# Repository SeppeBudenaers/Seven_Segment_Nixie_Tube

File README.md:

# Seven Segment Nixie Tube
 This repository contains the code and design files for a LED filament seven segment display, designed to resemble a nixie tube. The display can be configured in either common anode or WS2811 mode, providing a modern twist on the classic nixie tube aesthetic. It provides a warm glow to resemble a nixie tube while taking advantage of LED technology. Explore the provided files to build your own LED filament seven segment display and infuse your projects with a touch of vintage charm.
## How to use it 
To configure the LED filament seven segment display to common anode mode, solder the first and second pads of every solder bridge together.

To configure the LED filament seven segment display to WS2811 mode, solder the second and third pads of every solder bridge together.
## Bill of Material
### common anode mode

| Item                                   | Quantity | Link                                                                                                                                                       |
|----------------------------------------|----------|------------------------------------------------------------------------------------------------------------------------------------------------------------|
| Glas tube 30x60mm                      | x1       | [AliExpress Link](https://nl.aliexpress.com/item/32813289039.html?spm=a2g0o.order_list.order_list_main.5.21ef79d2e9LWZz&gatewayAdapt=glo2nld)                    |
| Red LED filament                       | x7       | [AliExpress Link](https://nl.aliexpress.com/item/1005003834518235.html?spm=a2g0o.order_list.order_list_main.10.21ef79d2e9LWZz&gatewayAdapt=glo2nld-)              |
| 47 ohm resistors                       | x7       | [LCSC Link](https://www.lcsc.com/product-detail/_UNI-ROYAL-Uniroyal-Elec-_C25315.html)                                                                    |
| 8 2,54mm pinheader reverse bending 90° | x1       | [AliExpress Link](https://nl.aliexpress.com/item/4000660389713.html?spm=a2g0o.productlist.main.5.6b8d804dlred9v&algo_pvid=283ea269-678a-498f-bd60-9fb64c34b0f6&algo_exp_id=283ea269-678a-498f-bd60-9fb64c34b0f6-2&pdp_npi=3%40dis%21EUR%210.67%210.62%21%21%21%21%21%402100b18f16839900715117374d078a%2110000005517155325%21sea%21BE%213754600235&curPageLogUid=IQMuIH5lTEpR) |

### WS2811 mode

| Item                                   | Quantity | Link                                                                                                                                                       |
|----------------------------------------|----------|------------------------------------------------------------------------------------------------------------------------------------------------------------|
| Glas tube 30x60mm                      | x1       | [AliExpress Link](https://nl.aliexpress.com/item/32813289039.html?spm=a2g0o.order_list.order_list_main.5.21ef79d2e9LWZz&gatewayAdapt=glo2nld)                    |
| Red LED filament                       | x7       | [AliExpress Link](https://nl.aliexpress.com/item/1005003834518235.html?spm=a2g0o.order_list.order_list_main.10.21ef79d2e9LWZz&gatewayAdapt=glo2nld)              |
| 47 ohm resistor                        | x7       | [LCSC Link](https://www.lcsc.com/product-detail/_UNI-ROYAL-Uniroyal-Elec-_C25315.html)                                                                    |
| 100 ohm resistor                       | x3       | [LCSC Link](https://www.lcsc.com/product-detail/_UNI-ROYAL-Uniroyal-Elec-_C17408.html)                                                                    |
| WS2811                                 | x3       | [LCSC Link](https://www.lcsc.com/product-detail/LED-Drivers_Worldsemi-WS2811_C114581.html)                                                                |
| 8 2,54mm pinheader reverse bending 90° | x1       | [AliExpress Link](https://nl.aliexpress.com/item/4000660389713.html?spm=a2g0o.productlist.main.5.6b8d804dlred9v&algo_pvid=283ea269-678a-498f-bd60-9fb64c34b0f6&algo_exp_id=283ea269-678a-498f-bd60-9fb64c34b0f6-2&pdp_npi=3%40dis%21EUR%210.67%210.62%21%21%21%21%21%402100b18f16839900715117374d078a%2110000005517155325%21sea%21BE%213754600235&curPageLogUid=IQMuIH5lTEpR) |

## todo
- [ ] Add media.
- [ ] Write a library for arduino to use my segments in WS2811 mode.

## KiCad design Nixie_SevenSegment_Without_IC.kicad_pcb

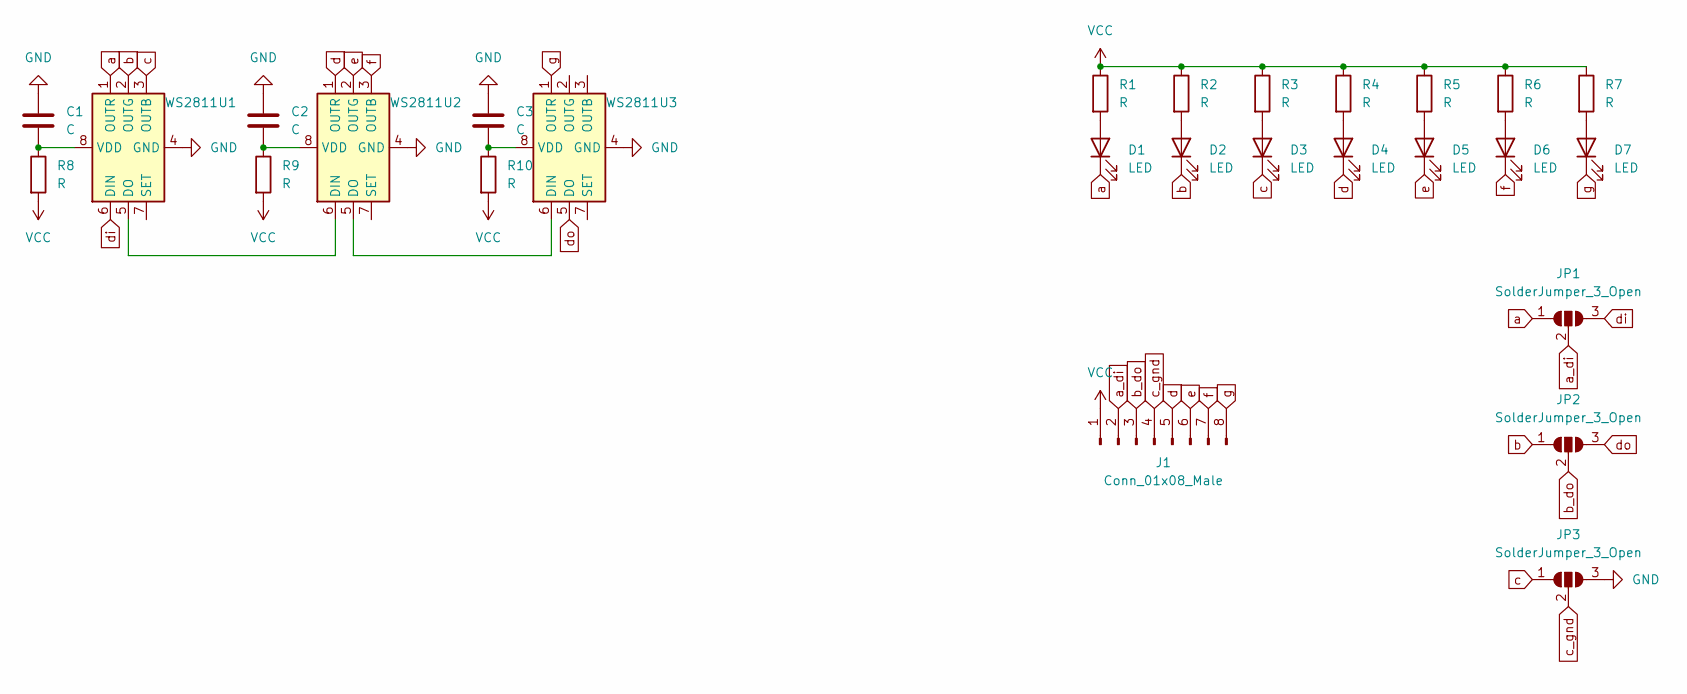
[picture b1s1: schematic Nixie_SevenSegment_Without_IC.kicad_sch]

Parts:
C1, C2, C3: C; C_0805_2012Metric_Pad1.18x1.45mm_HandSolder
D1, D2, D3, D4, D5, D6, D7: LED; LEDFilament_12mm
J1: Conn_01x08_Male; PinSocket_1x08_P2.54mm_Vertical
JP1, JP2, JP3: SolderJumper_3_Open; SolderJumper-3_P1.3mm_Open_Pad1.0x1.5mm
R1, R2, R3, R4, R5, R6, R7, R8, R9, R10: R; R_0805_2012Metric_Pad1.20x1.40mm_HandSolder
U1, U2, U3: WS2811; SOP-8_3.9x4.9mm_P1.27mm

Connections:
GND: C1.2, C2.2, C3.2, JP3.3 (B), U1.4 (GND), U2.4 (GND), U3.4 (GND)
unnamed: C1.1, R8.1, U1.8 (VDD)
unnamed: C2.1, R9.1, U2.8 (VDD)
unnamed: C3.1, R10.1, U3.8 (VDD)
unnamed: D1.2 (A), R1.2
unnamed: D2.2 (A), R2.2
unnamed: D3.2 (A), R3.2
unnamed: D4.2 (A), R4.2
unnamed: D5.2 (A), R5.2
unnamed: D6.2 (A), R6.2
unnamed: D7.2 (A), R7.2
unnamed: U1.5 (DO), U2.6 (DIN)
unnamed: U2.5 (DO), U3.6 (DIN)
VCC: J1.1, R1.1, R2.1, R3.1, R4.1, R5.1, R6.1, R7.1, R8.2, R9.2, R10.2
a: D1.1 (K), JP1.1 (A), U1.1 (OUTR)
a_di: J1.2, JP1.2 (C)
b: D2.1 (K), JP2.1 (A), U1.2 (OUTG)
b_do: J1.3, JP2.2 (C)
c: D3.1 (K), JP3.1 (A), U1.3 (OUTB)
c_gnd: J1.4, JP3.2 (C)
d: D4.1 (K), J1.5, U2.1 (OUTR)
di: JP1.3 (B), U1.6 (DIN)
do: JP2.3 (B), U3.5 (DO)
e: D5.1 (K), J1.6, U2.2 (OUTG)
f: D6.1 (K), J1.7, U2.3 (OUTB)
g: D7.1 (K), J1.8, U3.1 (OUTR)

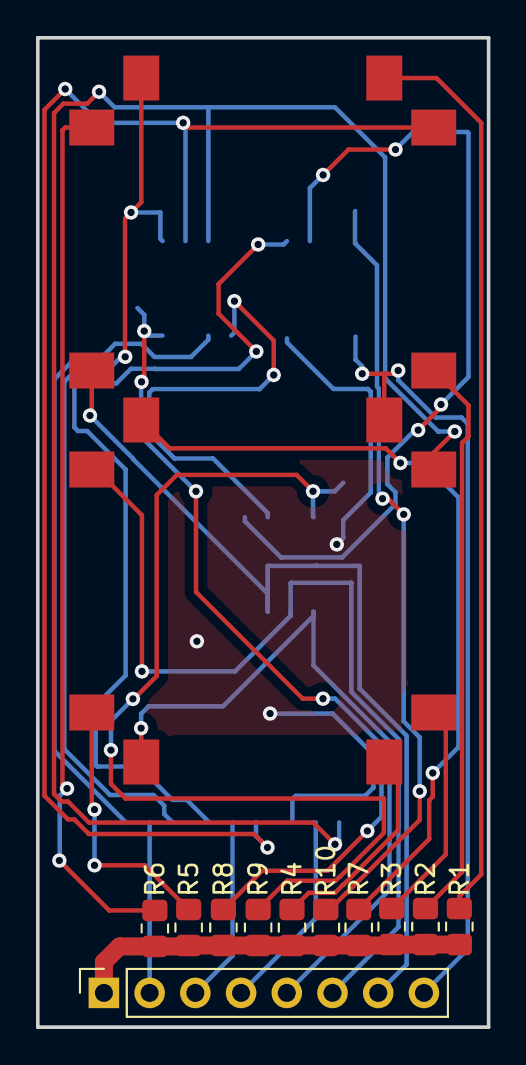
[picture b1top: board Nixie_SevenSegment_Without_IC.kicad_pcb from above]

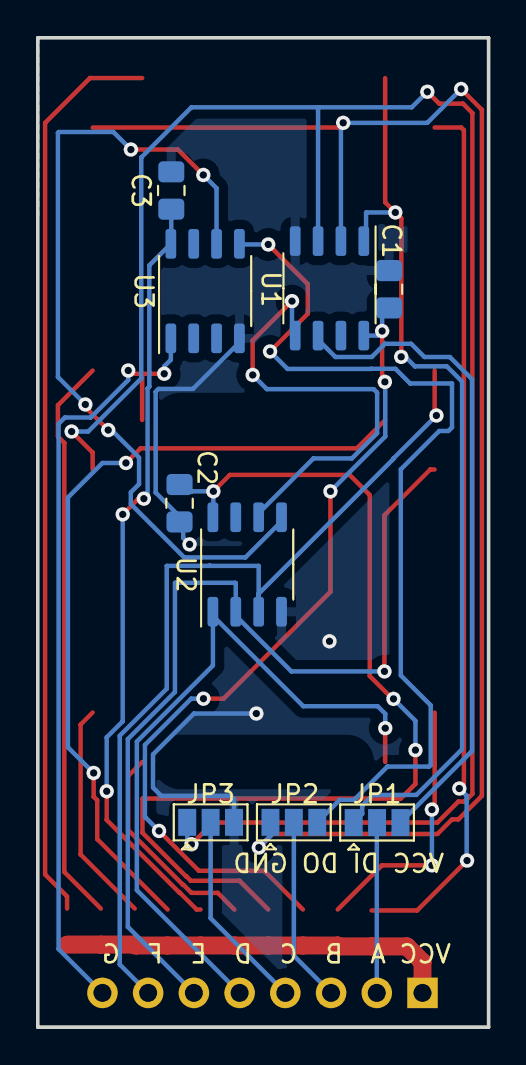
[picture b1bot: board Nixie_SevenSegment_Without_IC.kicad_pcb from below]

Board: 2 copper layers, 25.0 x 55.0 mm, 27 parts (9 on the bottom side), 26 nets.

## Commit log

2023-05-13 structure changes
2023-05-13 Update README.md
    added how to use and BOM
2023-05-13 added 3D cap
2023-05-13 added resistor values
2023-05-13 added to do list
2023-06-10 updated readability
    changed readme
    Made folder names more clear
    Added fusion 360 file for the segment
2024-06-30 added the ability to change segments with ws2812
